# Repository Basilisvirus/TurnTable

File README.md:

# TurnTable
A turning-table base (Antenna Positioner) for measuring radiation patterns

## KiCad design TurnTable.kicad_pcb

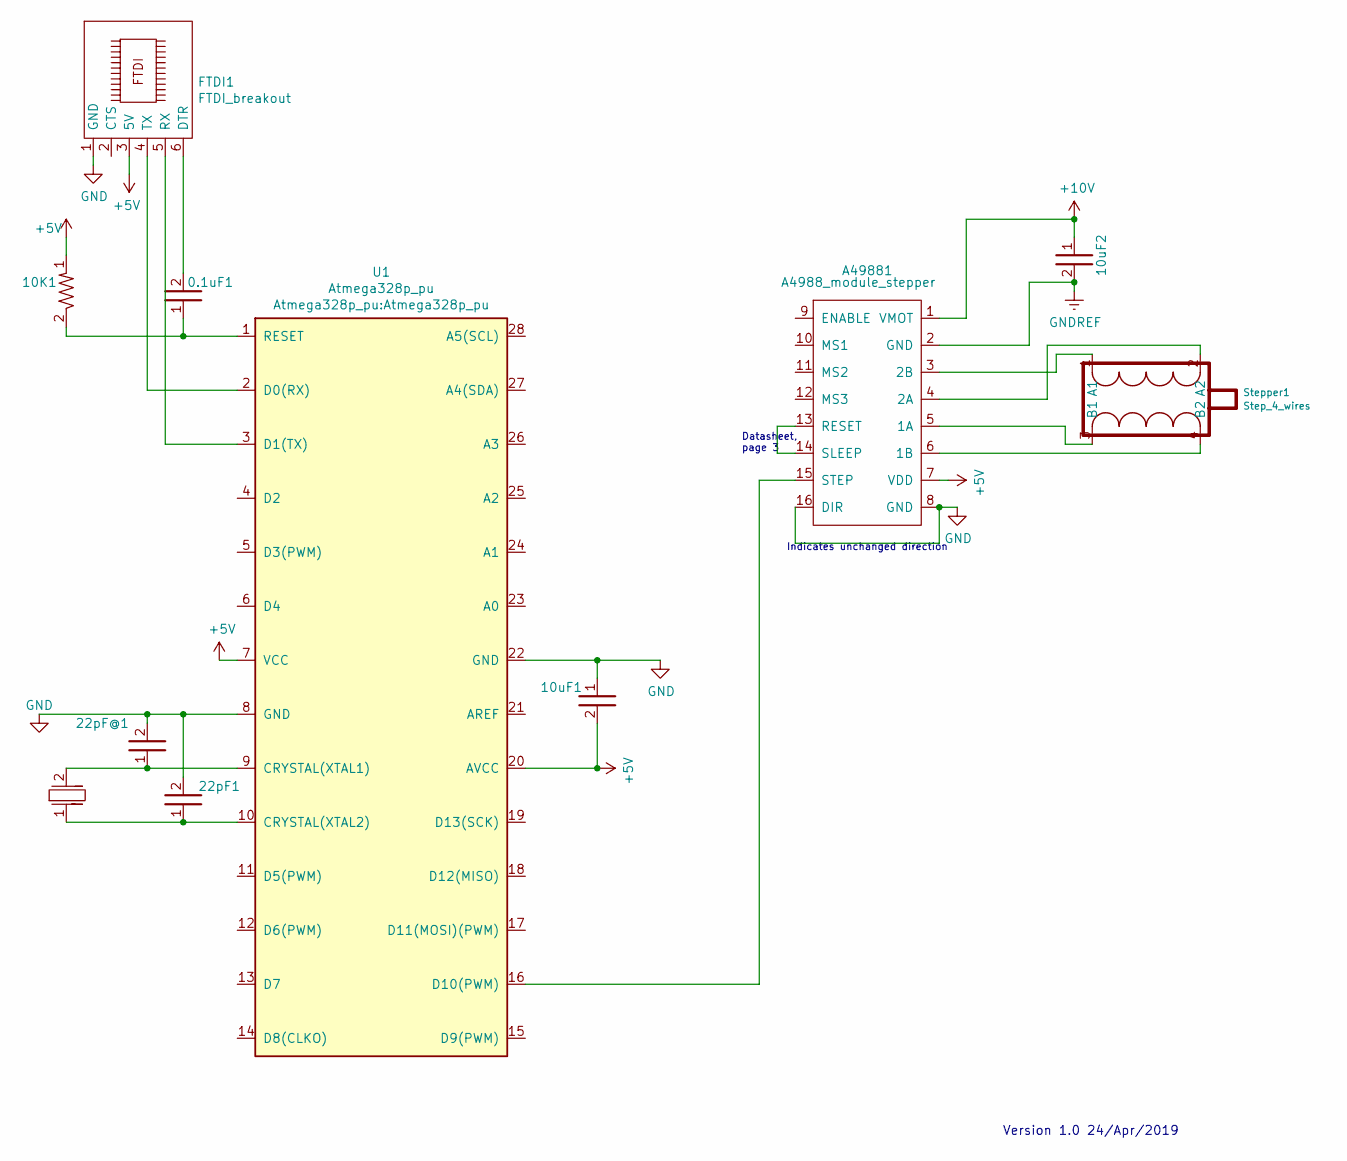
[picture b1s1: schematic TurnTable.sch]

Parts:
0.1uF1, 10uF1, 10uF2, 22pF1, 22pF@1: 1206_cap_smd
10K1: 1206_res_smd
A49881: A4988_module_stepper
FTDI1: FTDI_breakout
SR_H71: HC_49S
Stepper1: Step_4_wires
U1: Atmega328p_pu

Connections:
+5V: 10K1.1, 10uF1.2, A49881.7 (VDD), FTDI1.3 (5V), U1.7 (VCC), U1.20 (AVCC)
+10V: 10uF2.1, A49881.1 (VMOT)
GND: 10uF1.1, 22pF1.2, 22pF@1.2, A49881.8 (GND), A49881.16 (DIR), FTDI1.1 (GND), U1.8 (GND), U1.22 (GND)
GNDREF: 10uF2.2, A49881.2 (GND)
unnamed: 0.1uF1.1, 10K1.2, U1.1 (RESET)
unnamed: 0.1uF1.2, FTDI1.6 (DTR)
unnamed: 22pF1.1, SR_H71.1, U1.10 (CRYSTAL(XTAL2))
unnamed: 22pF@1.1, SR_H71.2, U1.9 (CRYSTAL(XTAL1))
unnamed: A49881.3 (2B), Stepper1.1 (A1)
unnamed: A49881.4 (2A), Stepper1.2 (A2)
unnamed: A49881.5 (1A), Stepper1.3 (B1)
unnamed: A49881.6 (1B), Stepper1.4 (B2)
unnamed: A49881.13 (RESET), A49881.14 (SLEEP)
unnamed: A49881.15 (STEP), U1.16 (D10(PWM))
unnamed: FTDI1.4 (TX), U1.2 (D0(RX))
unnamed: FTDI1.5 (RX), U1.3 (D1(TX))

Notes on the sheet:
Indicates unchanged direction
Datasheet, page 3
Version 1.0 24/Apr/2019

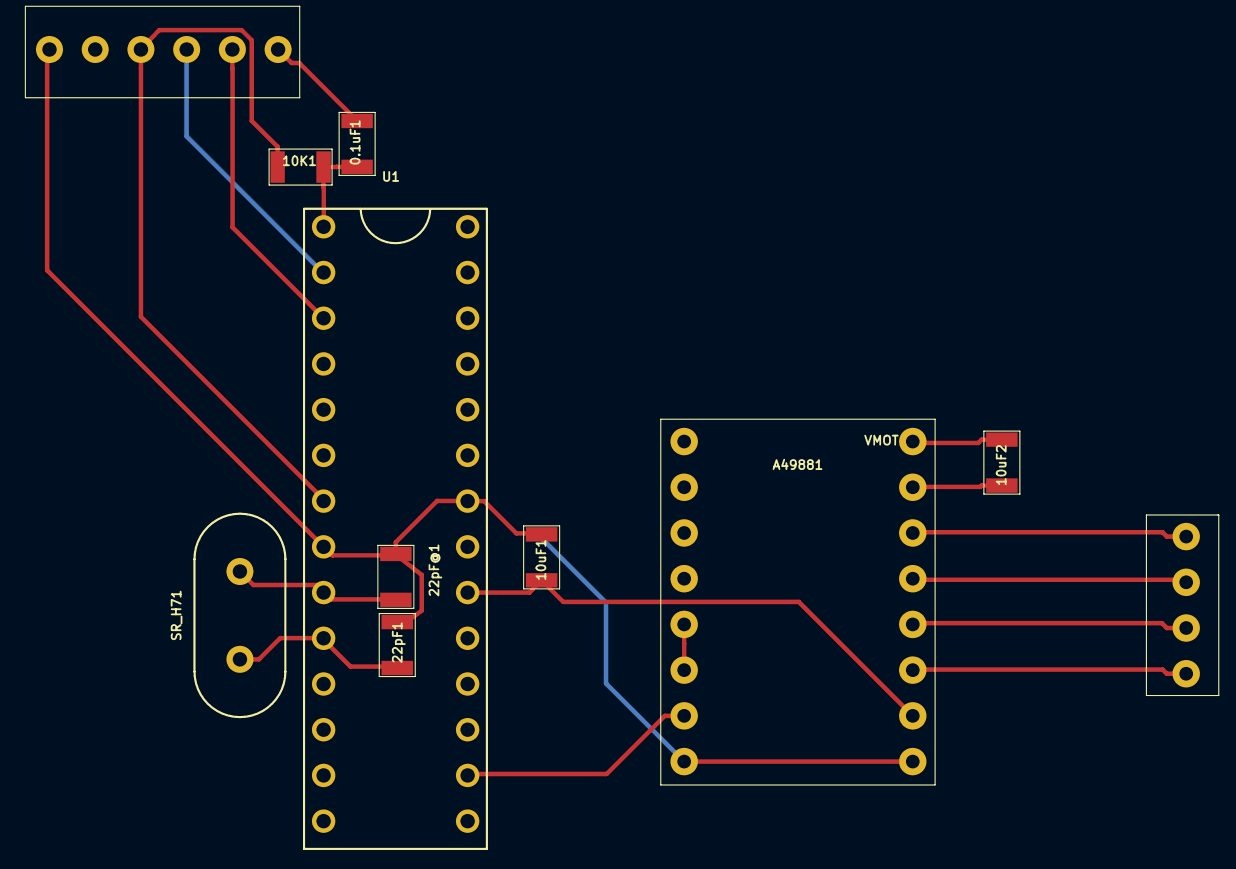
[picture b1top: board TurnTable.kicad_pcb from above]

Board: 2 copper layers, 11 parts (0 on the bottom side), 16 nets.

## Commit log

2019-04-25 test upload
2019-06-18 none
